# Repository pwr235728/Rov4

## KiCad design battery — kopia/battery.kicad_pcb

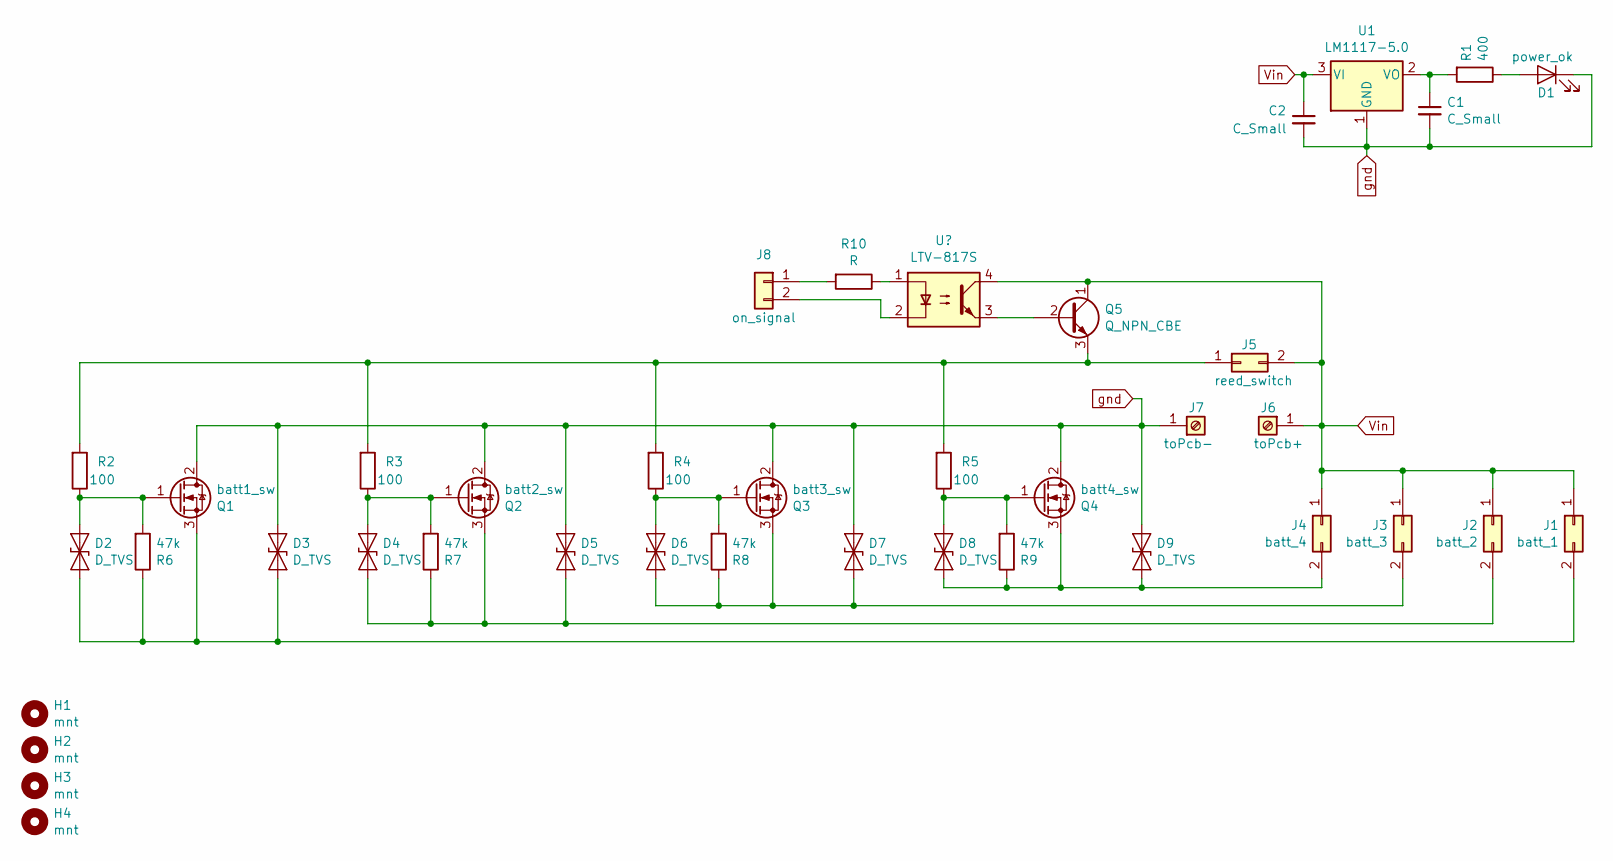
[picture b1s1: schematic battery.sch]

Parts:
C1, C2: C_Small; C_0805_2012Metric_Pad1.15x1.40mm_HandSolder
D1: power_ok; LED_0805_2012Metric
D2, D3, D4, D5, D6, D7, D8, D9: D_TVS; D_SMB_Handsoldering
H1, H2, H3, H4: mnt; MountingHole_2.2mm_M2_DIN965_Pad
J1: batt_1; XT60UPB-M
J2: batt_2; XT60UPB-M
J3: batt_3; XT60UPB-M
J4: batt_4; XT60UPB-M
J5: reed_switch; Molex_SPOX_5267-02A_1x02_P2.50mm_Vertical
J6: toPcb+; MountingHole_4.3mm_M4_DIN965_Pad
J7: toPcb-; MountingHole_4.3mm_M4_DIN965_Pad
J8: on_signal; Molex_SPOX_5267-02A_1x02_P2.50mm_Vertical
Q1: batt1_sw; TO-252-2
Q2: batt2_sw; TO-252-2
Q3: batt3_sw; TO-252-2
Q4: batt4_sw; TO-252-2
Q5: Q_NPN_CBE; TO-92
R1: 400; R_0805_2012Metric
R2, R3, R4, R5: 100; R_0805_2012Metric
R6, R7, R8, R9: 47k; R_0805_2012Metric
R10: R; R_0805_2012Metric_Pad1.15x1.40mm_HandSolder
U1: LM1117-5.0; SOT-223-3_TabPin2

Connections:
unnamed: C1.1, R1.2, U1.2 (VO)
unnamed: D1.2 (A), R1.1
unnamed: D2.1 (A1), Q1.1 (G), R2.1, R6.2
unnamed: D2.2 (A2), D3.2 (A2), J1.2, Q1.3 (S), R6.1
unnamed: D4.1 (A1), Q2.1 (G), R3.1, R7.2
unnamed: D4.2 (A2), D5.2 (A2), J2.2, Q2.3 (S), R7.1
unnamed: D6.1 (A1), Q3.1 (G), R4.1, R8.2
unnamed: D6.2 (A2), D7.2 (A2), J3.2, Q3.3 (S), R8.1
unnamed: D8.1 (A1), Q4.1 (G), R5.1, R9.2
unnamed: D8.2 (A2), D9.2 (A2), J4.2, Q4.3 (S), R9.1
unnamed: J5.1, Q5.3 (E), R2.2, R3.2, R4.2, R5.2
unnamed: J8.1, R10.2
unnamed 12: J8.2; also elsewhere on the board
unnamed 13: Q5.2 (B); also elsewhere on the board
unnamed 14: R10.1; also elsewhere on the board
Vin: C2.1, J1.1, J2.1, J3.1, J4.1, J5.2, J6.1, Q5.1 (C), U1.3 (VI); also elsewhere on the board
gnd: C1.2, C2.2, D1.1 (K), D3.1 (A1), D5.1 (A1), D7.1 (A1), D9.1 (A1), J7.1, Q1.2 (D), Q2.2 (D), Q3.2 (D), Q4.2 (D), U1.1 (GND)

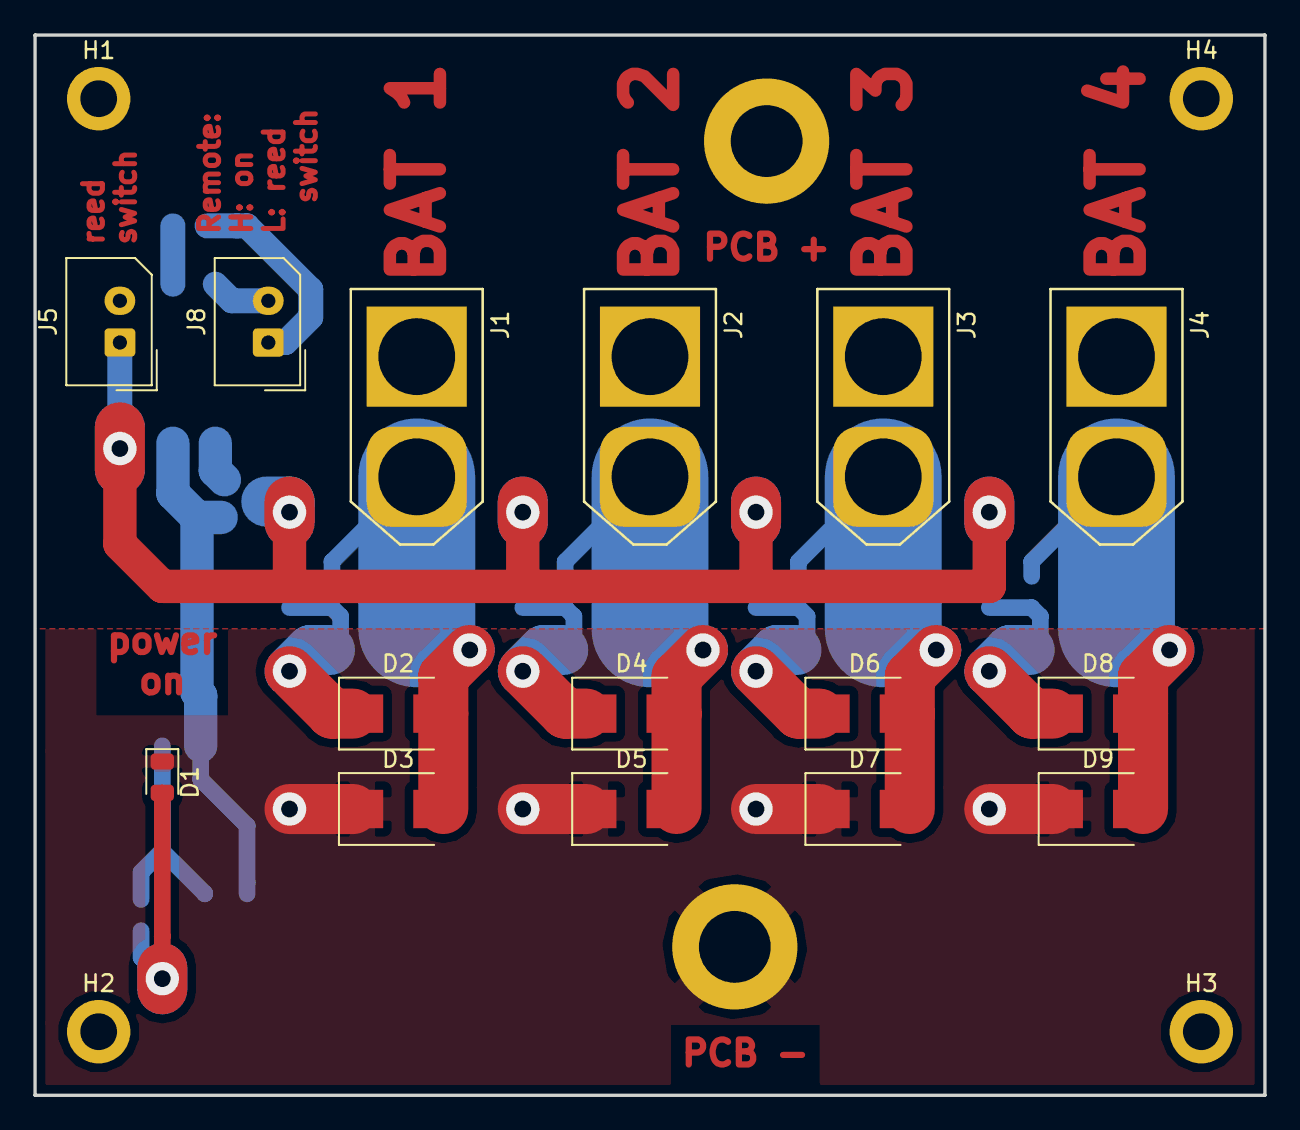
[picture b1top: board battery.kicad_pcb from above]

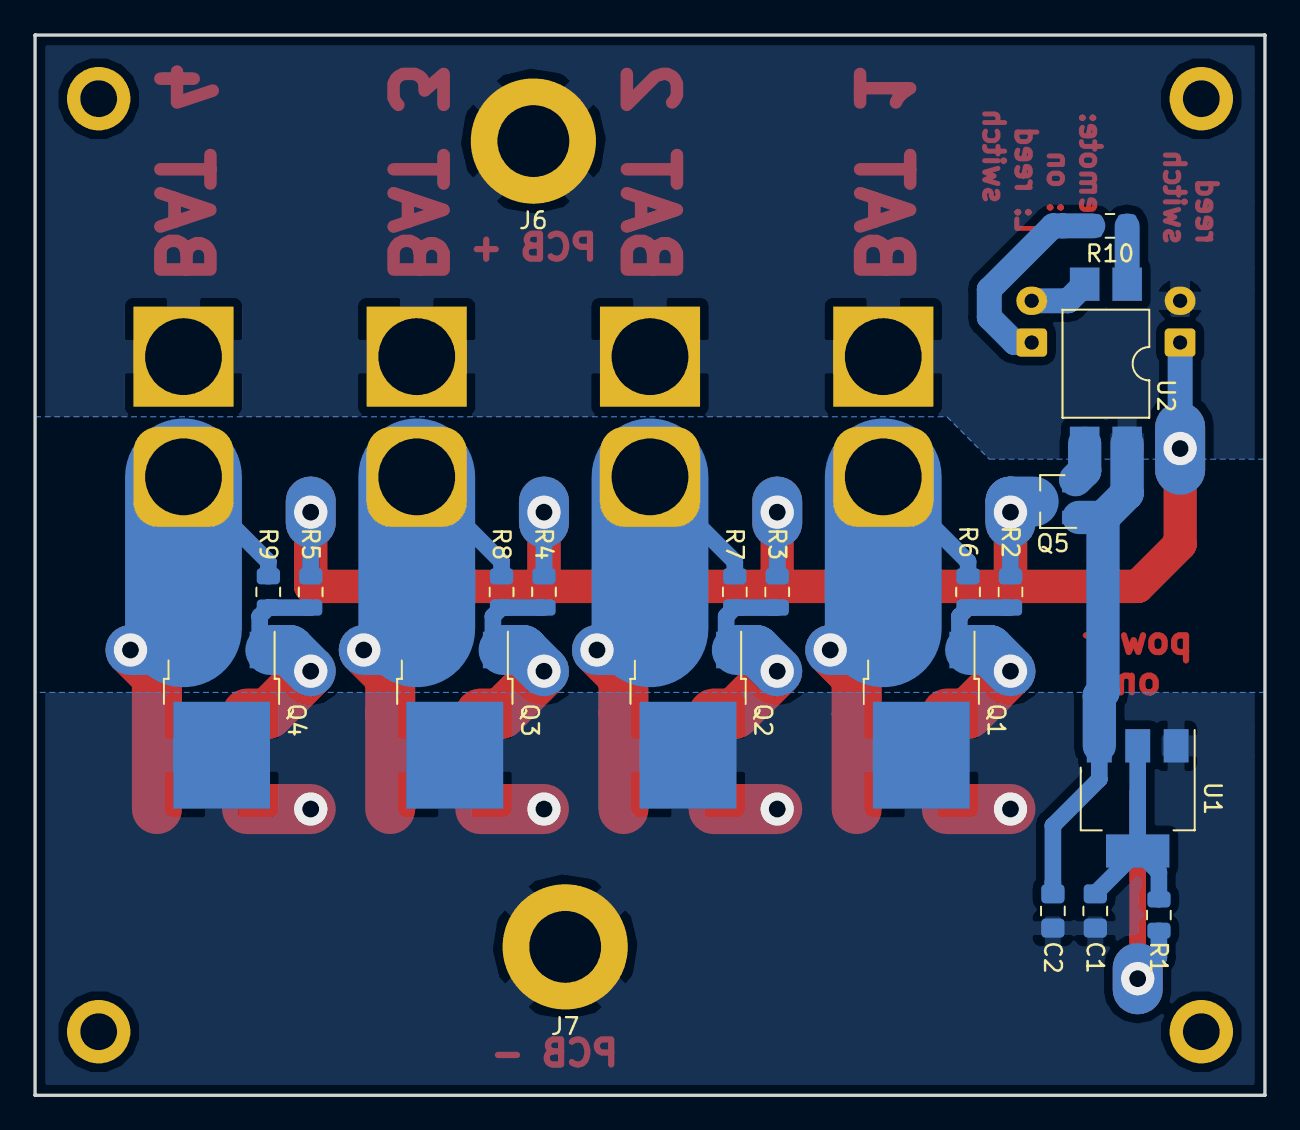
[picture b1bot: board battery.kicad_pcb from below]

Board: 2 copper layers, 73.7 x 63.5 mm, 40 parts (21 on the bottom side), 17 nets.

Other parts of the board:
U2: LTV-817S; SMDIP-4_W9.53mm

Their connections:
unnamed 12: U2.2; also elsewhere on the board
unnamed 13: U2.3; also elsewhere on the board
unnamed 14: U2.1; also elsewhere on the board
Vin: U2.4; also elsewhere on the board

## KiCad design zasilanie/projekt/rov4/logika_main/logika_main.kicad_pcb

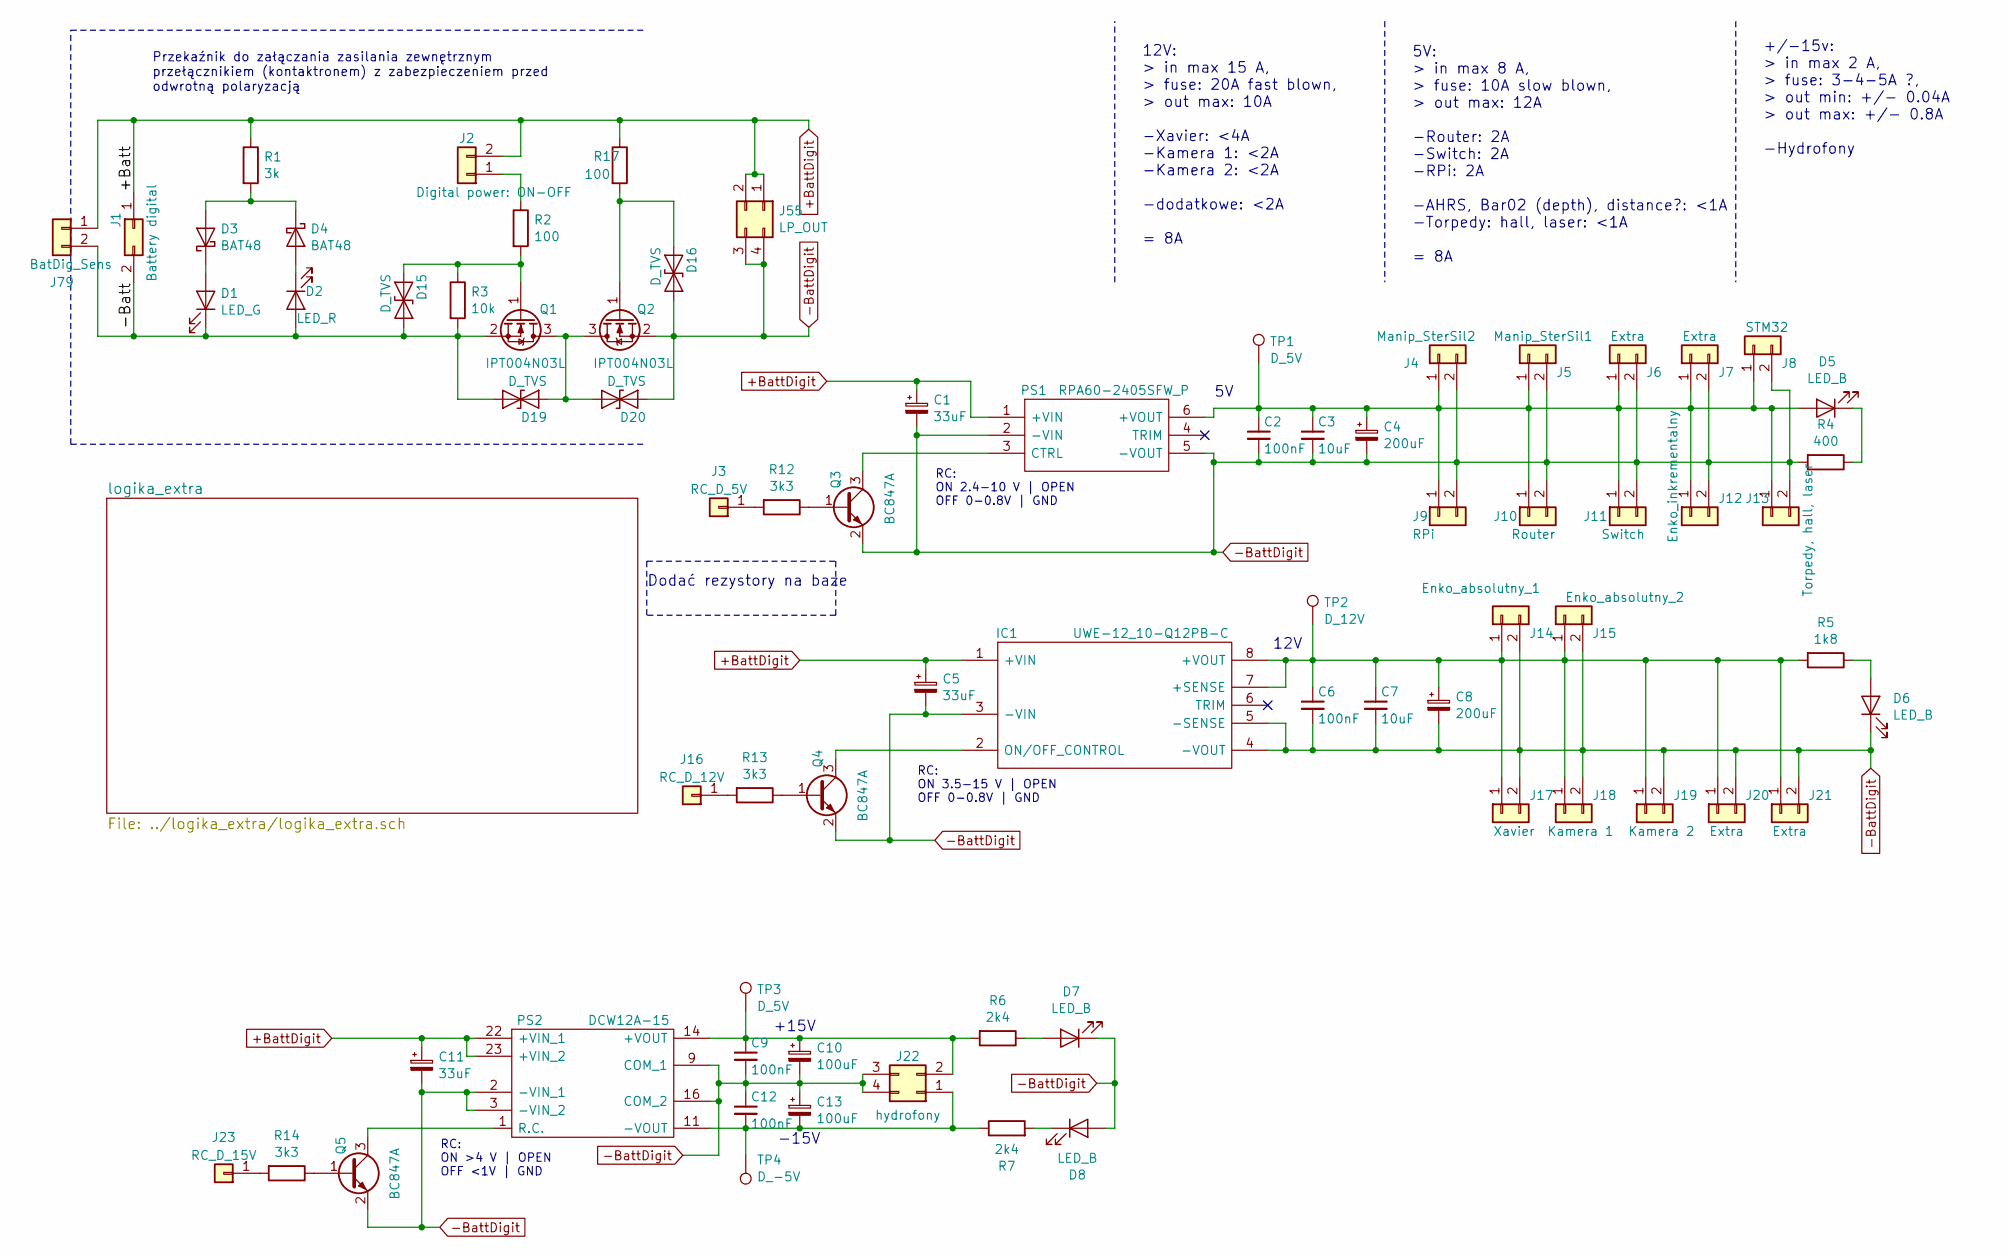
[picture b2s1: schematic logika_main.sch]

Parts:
C1, C5, C11: 33uF; CP_Elec_6.3x5.4
C2, C6, C9, C12: 100nF; C_0805_2012Metric
C3, C7: 10uF; C_0805_2012Metric
C4, C8: 200uF; CP_Elec_8x10
C10, C13: 100uF; CP_Elec_6.3x7.7
D1: LED_G; LED_0805_2012Metric
D2: LED_R; LED_0805_2012Metric
D3, D4: BAT48; D_MiniMELF
D5, D6, D7, D8: LED_B; LED_0805_2012Metric
D15, D16, D19, D20: D_TVS; D_SMB
IC1: UWE-12_10-Q12PB-C; UWE-12_10-Q12P-C; Mouser Part Number 580-UWE-12/10Q12PBC
J1: Battery digital; XT60UPB-M
J2: Digital power: ON-OFF; Molex_SPOX_5267-02A_1x02_P2.50mm_Vertical
J3: RC_D_5V; Molex_SPOX_5267-02A_1x02_P2.50mm_Vertical
J4: Manip_SterSil2; Molex_Mini-Fit_Jr_5566-02A_2x01_P4.20mm_Vertical
J5: Manip_SterSil1; Molex_Mini-Fit_Jr_5566-02A_2x01_P4.20mm_Vertical
J6, J7, J20, J21: Extra; Molex_Mini-Fit_Jr_5566-02A_2x01_P4.20mm_Vertical
J8: STM32; Molex_Mini-Fit_Jr_5566-02A_2x01_P4.20mm_Vertical
J9: RPi; Molex_Mini-Fit_Jr_5566-02A_2x01_P4.20mm_Vertical
J10: Router; Molex_Mini-Fit_Jr_5566-02A_2x01_P4.20mm_Vertical
J11: Switch; Molex_Mini-Fit_Jr_5566-02A_2x01_P4.20mm_Vertical
J12: Enko_inkrementalny; Molex_Mini-Fit_Jr_5566-02A_2x01_P4.20mm_Vertical
J13: Torpedy, hall, laser; Molex_Mini-Fit_Jr_5566-02A_2x01_P4.20mm_Vertical
J14: Enko_absolutny_1; Molex_Mini-Fit_Jr_5566-02A_2x01_P4.20mm_Vertical
J15: Enko_absolutny_2; Molex_Mini-Fit_Jr_5566-02A_2x01_P4.20mm_Vertical
J16: RC_D_12V; Molex_SPOX_5267-02A_1x02_P2.50mm_Vertical
J17: Xavier; Molex_Mini-Fit_Jr_5566-02A_2x01_P4.20mm_Vertical
J18: Kamera 1; Molex_Mini-Fit_Jr_5566-02A_2x01_P4.20mm_Vertical
J19: Kamera 2; Molex_Mini-Fit_Jr_5566-02A_2x01_P4.20mm_Vertical
J22: hydrofony; Molex_Mini-Fit_Jr_5566-04A_2x02_P4.20mm_Vertical
J23: RC_D_15V; Molex_SPOX_5267-02A_1x02_P2.50mm_Vertical
J55: LP_OUT; Molex_Mini-Fit_Jr_5566-04A_2x02_P4.20mm_Vertical
J79: BatDig_Sens; Molex_SPOX_5267-02A_1x02_P2.50mm_Vertical
PS1: RPA60-2405SFW_P; Mouser Part Number 919-RPA60-2415SFW/P
PS2: DCW12A-15; Manufacturer_Part_Number DCW12A-15
Q1, Q2: IPT004N03L; Infineon_PG-HSOF-8-1
Q3, Q4, Q5: BC847A; SOT-23
R1: 3k; R_0805_2012Metric
R2, R17: 100; R_0805_2012Metric
R3: 10k; R_0805_2012Metric
R4: 400; R_0805_2012Metric
R5: 1k8; R_0805_2012Metric
R6, R7: 2k4; R_0805_2012Metric
R12, R13, R14: 3k3; R_0805_2012Metric
TP1, TP3: D_5V; PinHeader_1x01_P2.54mm_Vertical
TP2: D_12V; PinHeader_1x01_P2.54mm_Vertical
TP4: D_-5V; PinHeader_1x01_P2.54mm_Vertical

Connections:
+BattDigit: C1.1, C5.1, C11.1, IC1.1 (+VIN), J1.1, J2.2, J55.1, J55.2, J79.1, PS1.1 (+VIN), PS2.22 (+VIN_1), PS2.23 (+VIN_2), R1.1, R17.1
-BattDigit: C1.2, C2.2, C3.2, C4.2, C5.2, C6.2, C7.2, C8.2, C9.2, C10.2, C11.2, C12.1, C13.1, D6.1 (K), D7.1 (K), D8.2 (A), D16.2 (A2), D20.1 (A1), IC1.3 (-VIN), IC1.4 (-VOUT), IC1.5 (-SENSE), J4.2, J5.2, J6.2, J7.2, J8.2, J9.2, J10.2, J11.2, J12.2, J13.2, J14.2, J15.2, J17.2, J18.2, J19.2, J20.2, J21.2, J22.3, J22.4, J55.3, J55.4, PS1.2 (-VIN), PS1.5 (-VOUT), PS2.2 (-VIN_1), PS2.3 (-VIN_2), PS2.9 (COM_1), PS2.16 (COM_2), Q2.2 (S), Q3.2 (E), Q4.2 (E), Q5.2 (E), R4.2
/logika_main/-Batt: D1.1 (K), D2.2 (A), D15.2 (A2), D19.2 (A2), J1.2, J79.2, Q1.2 (S), R3.2
unnamed: C2.1, C3.1, C4.1, D5.2 (A), J4.1, J5.1, J6.1, J7.1, J8.1, J9.1, J10.1, J11.1, J12.1, J13.1, PS1.6 (+VOUT), TP1.1
unnamed: C6.1, C7.1, C8.1, IC1.7 (+SENSE), IC1.8 (+VOUT), J14.1, J15.1, J17.1, J18.1, J19.1, J20.1, J21.1, R5.2, TP2.1
unnamed: C9.1, C10.1, J22.2, PS2.14 (+VOUT), R6.2, TP3.1
unnamed: C12.2, C13.2, J22.1, PS2.11 (-VOUT), R7.1, TP4.1
unnamed: D1.2 (A), D3.1 (K)
unnamed: D2.1 (K), D4.2 (A)
unnamed: D3.2 (A), D4.1 (K), R1.2
unnamed: D5.1 (K), R4.1
unnamed: D6.2 (A), R5.1
unnamed: D7.2 (A), R6.1
unnamed: D8.1 (K), R7.2
unnamed: D15.1 (A1), Q1.1 (G), R2.2, R3.1
unnamed: D16.1 (A1), Q2.1 (G), R17.2
unnamed: D19.1 (A1), D20.2 (A2), Q1.3 (D), Q2.3 (D)
unnamed: IC1.2 (ON/OFF_CONTROL), Q4.3 (C)
unnamed: J2.1, R2.1
unnamed: J3.1, R12.2
unnamed: J16.1, R13.2
unnamed: J23.1, R14.2
unnamed: PS1.3 (CTRL), Q3.3 (C)
unnamed: PS2.1 (R.C.), Q5.3 (C)
unnamed: Q3.1 (B), R12.1
unnamed: Q4.1 (B), R13.1
unnamed: Q5.1 (B), R14.1

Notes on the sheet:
Przekaźnik do załączania zasilania zewnętrznym przełącznikiem (kontaktronem) z zabezpieczeniem przed odwrotną polaryzacją
RC: ON 3.5-15 V | OPEN OFF 0-0.8V | GND
RC: ON 2.4-10 V | OPEN OFF 0-0.8V | GND
12V
RC: ON >4 V | OPEN OFF <1V | GND
+15V
-15V
5V: > in max 8 A, > fuse: 10A slow blown, > out max: 12A -Router: 2A -Switch: 2A -RPi: 2A -AHRS, Bar02 (depth), distance?: <1A -Torpedy: hall, laser: <1A = 8A
+/-15v: > in max 2 A, > fuse: 3-4-5A ?, > out min: +/- 0.04A > out max: +/- 0.8A -Hydrofony
12V: > in max 15 A, > fuse: 20A fast blown, > out max: 10A -Xavier: <4A -Kamera 1: <2A -Kamera 2: <2A -dodatkowe: <2A = 8A
Dodać rezystory na baze

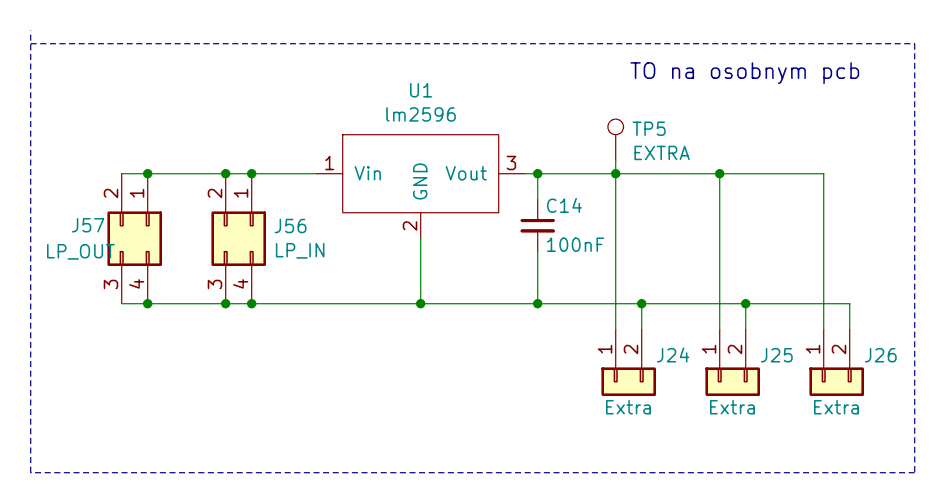
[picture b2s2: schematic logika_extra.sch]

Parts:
C14: 100nF; C_0805_2012Metric
J24, J25, J26: Extra; Molex_Mini-Fit_Jr_5566-02A_2x01_P4.20mm_Vertical
J56: LP_IN; Molex_Mini-Fit_Jr_5566-04A_2x02_P4.20mm_Vertical
J57: LP_OUT; Molex_Mini-Fit_Jr_5566-04A_2x02_P4.20mm_Vertical
TP5: EXTRA; PinHeader_1x01_P2.54mm_Vertical
U1: lm2596; lm2596-44_8mm_x_23mm

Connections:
unnamed: C14.1, J24.1, J25.1, J26.1, TP5.1, U1.3 (Vout)
unnamed: C14.2, J24.2, J25.2, J26.2, J56.3, J56.4, J57.3, J57.4, U1.2 (GND), U1.4 (GND)
unnamed: J56.1, J56.2, J57.1, J57.2, U1.1 (Vin)

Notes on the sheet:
TO na osobnym pcb

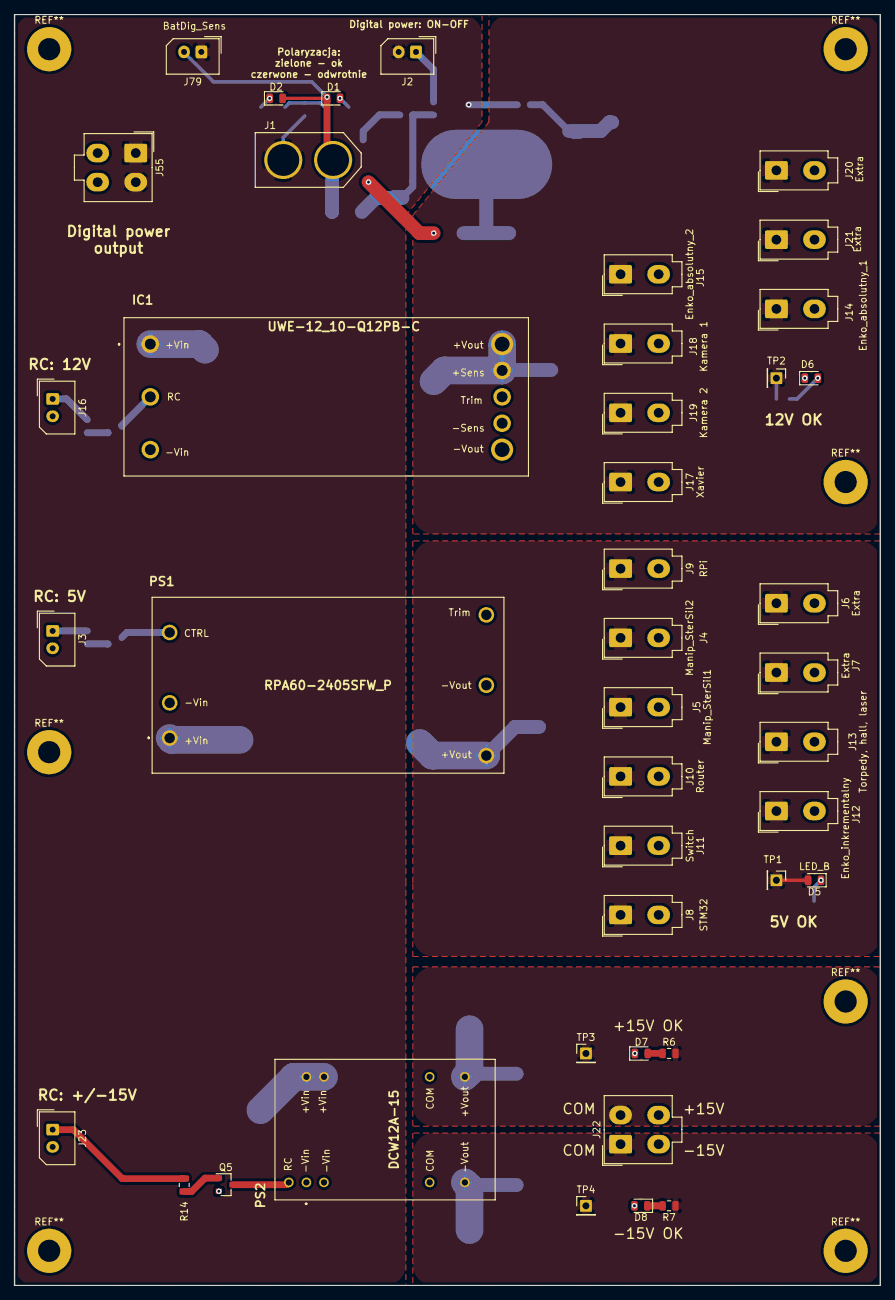
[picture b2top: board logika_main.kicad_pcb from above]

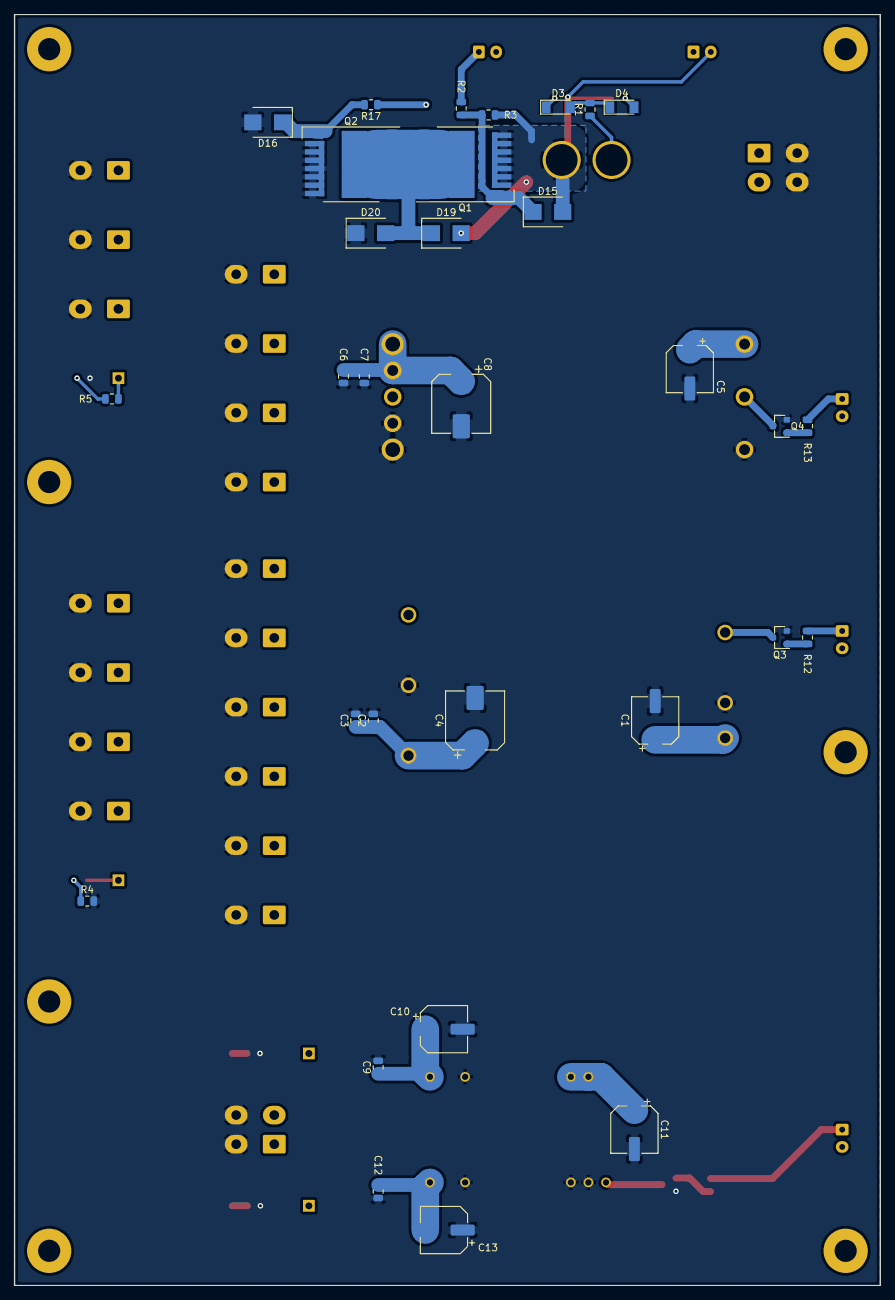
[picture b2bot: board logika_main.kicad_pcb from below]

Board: 2 copper layers, 125.0 x 183.5 mm, 73 parts (31 on the bottom side), 27 nets.

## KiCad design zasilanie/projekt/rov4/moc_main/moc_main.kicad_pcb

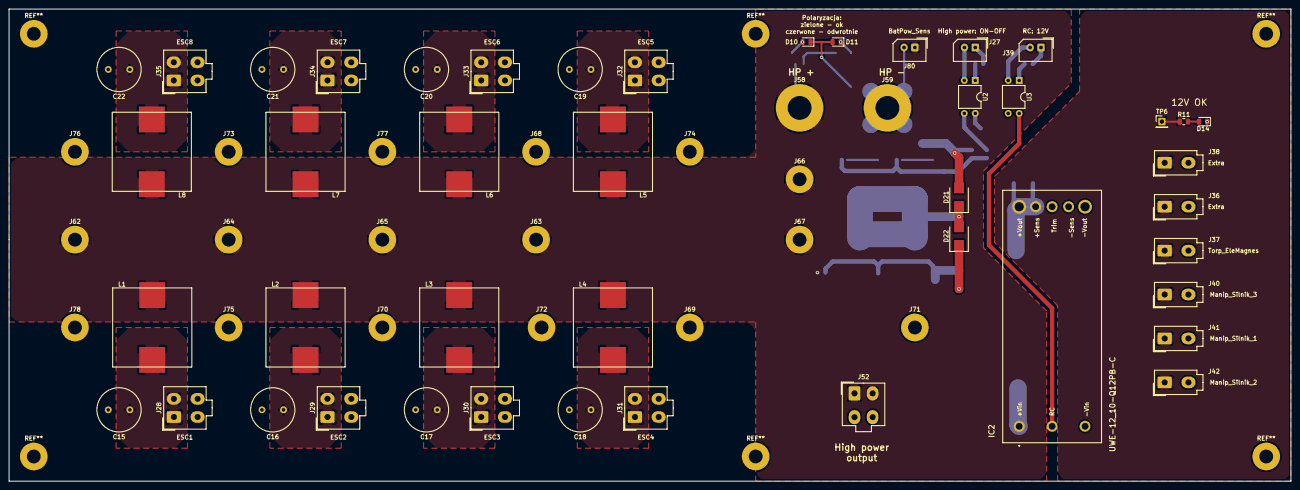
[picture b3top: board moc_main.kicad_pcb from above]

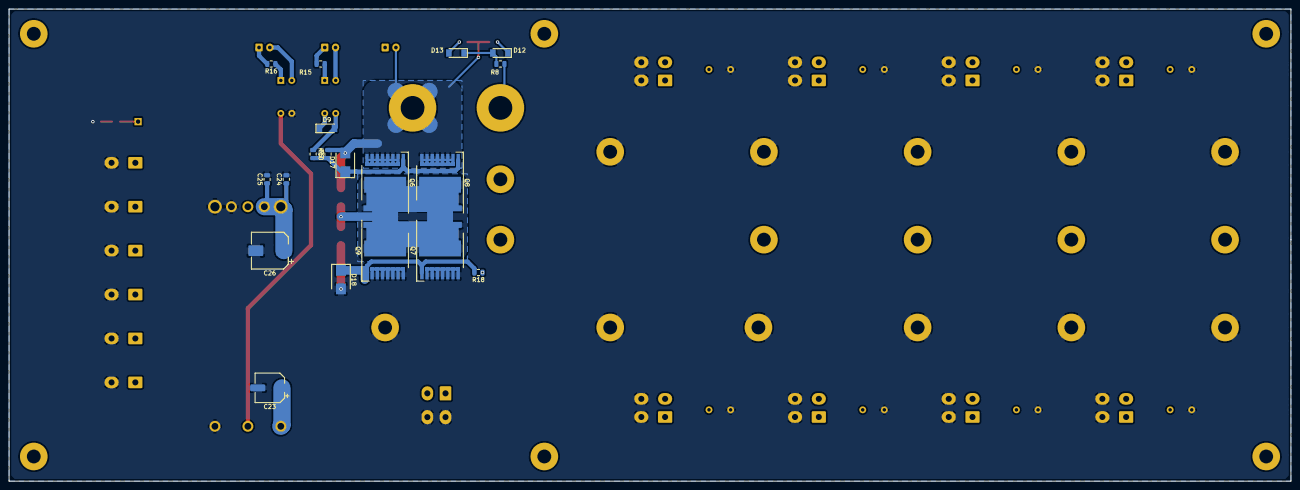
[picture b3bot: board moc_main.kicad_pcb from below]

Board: 2 copper layers, 296.5 x 109.2 mm, 82 parts (19 on the bottom side), 27 nets.

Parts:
C15, C16, C17, C18, C19, C20, C21, C22: C; C_Radial_D10.0mm_H20.0mm_P5.00mm
C23: 33uF; CP_Elec_6.3x5.4
C24: 100nF; C_0805_2012Metric
C25: 10uF; C_0805_2012Metric
C26: 200uF; CP_Elec_8x10
D9, D12, D13: BAT48; D_MiniMELF
D10: LED_G; LED_0805_2012Metric
D11: LED_R; LED_0805_2012Metric
D14: LED_B; LED_0805_2012Metric
D17, D18, D21, D22: D_TVS; D_SMB
IC2: UWE-12_10-Q12PB-C; UWE-12_10-Q12P-C
J27: High power: ON-OFF; Molex_SPOX_5267-02A_1x02_P2.50mm_Vertical
J28: ESC1; Molex_Mini-Fit_Jr_5566-04A_2x02_P4.20mm_Vertical
J29: ESC2; Molex_Mini-Fit_Jr_5566-04A_2x02_P4.20mm_Vertical
J30: ESC3; Molex_Mini-Fit_Jr_5566-04A_2x02_P4.20mm_Vertical
J31: ESC4; Molex_Mini-Fit_Jr_5566-04A_2x02_P4.20mm_Vertical
J32: ESC5; Molex_Mini-Fit_Jr_5566-04A_2x02_P4.20mm_Vertical
J33: ESC6; Molex_Mini-Fit_Jr_5566-04A_2x02_P4.20mm_Vertical
J34: ESC7; Molex_Mini-Fit_Jr_5566-04A_2x02_P4.20mm_Vertical
J35: ESC8; Molex_Mini-Fit_Jr_5566-04A_2x02_P4.20mm_Vertical
J36, J38: Extra; Molex_Mini-Fit_Jr_5566-02A_2x01_P4.20mm_Vertical
J37: Torp_EleMagnes; Molex_Mini-Fit_Jr_5566-02A_2x01_P4.20mm_Vertical
J39: RC: 12V; Molex_SPOX_5267-02A_1x02_P2.50mm_Vertical
J40: Manip_Silnik_3; Molex_Mini-Fit_Jr_5566-02A_2x01_P4.20mm_Vertical
J41: Manip_Silnik_1; Molex_Mini-Fit_Jr_5566-02A_2x01_P4.20mm_Vertical
J42: Manip_Silnik_2; Molex_Mini-Fit_Jr_5566-02A_2x01_P4.20mm_Vertical
J52: HP_OUT; Molex_Mini-Fit_Jr_5566-04A_2x02_P4.20mm_Vertical
J58: +BattPower; MountingHole_5.5mm_Pad
J59: -BattPower; MountingHole_5.5mm_Pad
J62, J63, J64, J65, J66, J67: bus_bar; MountingHole_3.2mm_M3_Pad
J68, J69, J70, J71, J72, J73, J74, J75, J76, J77, J78: bus_bar_bott; MountingHole_3.2mm_M3_Pad
J80: BatPow_Sens; Molex_SPOX_5267-02A_1x02_P2.50mm_Vertical
L1, L2, L3, L4, L5, L6, L7, L8: L; 74435571100
Q6, Q7, Q8, Q9: IPT004N03L; Infineon_PG-HSOF-8-1
R8: 3k; R_0805_2012Metric
R9, R18: 100; R_0805_2012Metric
R10: 10k; R_0805_2012Metric
R11: 1k8; R_0805_2012Metric
R15, R16: 680; R_0805_2012Metric
TP6: HP_12V; PinHeader_1x01_P2.54mm_Vertical
U2, U3: Transoptor; DIP-4_W7.62mm

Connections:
+BattPow: C23.1, D9.1, IC2.1, J52.1, J52.2, J58.1, J62.1, J63.1, J64.1, J65.1, J66.1, J67.1, J80.1, L1.1, L2.1, L3.1, L4.1, L5.1, L6.1, L7.1, L8.1, R8.1, R18.1, U2.4
-BattPow: C15.2, C16.2, C17.2, C18.2, C19.2, C20.2, C21.2, C22.2, C23.2, C24.2, C25.2, C26.2, D14.1, D18.2, D22.1, IC2.3, IC2.4, IC2.5, J28.3, J28.4, J29.3, J29.4, J30.3, J30.4, J31.3, J31.4, J32.3, J32.4, J33.3, J33.4, J34.3, J34.4, J35.3, J35.4, J36.2, J37.2, J38.2, J40.2, J41.2, J42.2, J52.3, J52.4, J68.1, J69.1, J70.1, J71.1, J72.1, J73.1, J74.1, J75.1, J76.1, J77.1, J78.1, Q7.2, Q9.2, U3.3
unnamed: C15.1, J28.1, J28.2, L1.2
unnamed: C16.1, J29.1, J29.2, L2.2
unnamed: C17.1, J30.1, J30.2, L3.2
unnamed: C18.1, J31.1, J31.2, L4.2
unnamed: C19.1, J32.1, J32.2, L5.2
unnamed: C20.1, J33.1, J33.2, L6.2
unnamed: C21.1, J34.1, J34.2, L7.2
unnamed: C22.1, J35.1, J35.2, L8.2
unnamed: C24.1, C25.1, C26.1, IC2.7, IC2.8, J36.1, J37.1, J38.1, J40.1, J41.1, J42.1, R11.1, TP6.1
unnamed: D9.2, R9.1, U2.3
unnamed: D10.1, D11.2, D17.2, D21.2, J59.1, J80.2, Q6.2, Q8.2, R10.2
unnamed: D10.2, D12.1
unnamed: D11.1, D13.2
unnamed: D12.2, D13.1, R8.2
unnamed: D14.2, R11.2
unnamed: D17.1, Q6.1, Q8.1, R9.2, R10.1
unnamed: D18.1, Q7.1, Q9.1, R18.2
unnamed: D21.1, D22.2, Q6.3, Q7.3, Q8.3, Q9.3
unnamed: IC2.2, U3.4
unnamed: J27.1, R15.2
unnamed: J27.2, U2.2
unnamed: J39.1, R16.2
unnamed: J39.2, U3.2
unnamed: R15.1, U2.1
unnamed: R16.1, U3.1
